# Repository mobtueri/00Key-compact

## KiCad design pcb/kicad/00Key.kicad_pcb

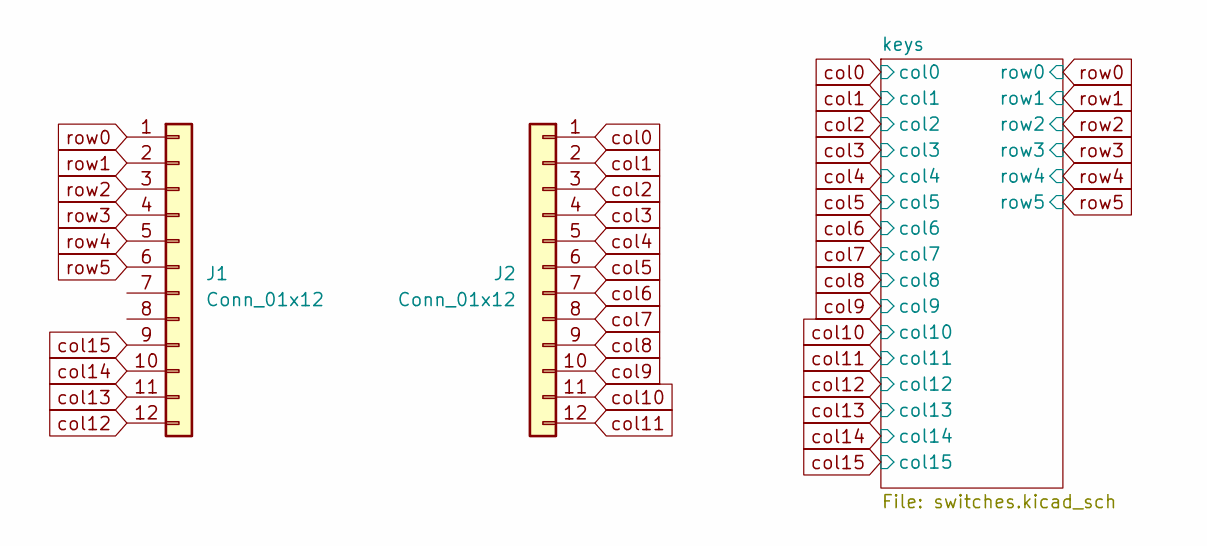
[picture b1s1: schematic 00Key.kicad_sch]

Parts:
J1, J2: Conn_01x12; PinSocket_1x12_P2.54mm_Horizontal

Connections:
col0: J2.1; also elsewhere on the board
col1: J2.2; also elsewhere on the board
col2: J2.3; also elsewhere on the board
col3: J2.4; also elsewhere on the board
col4: J2.5; also elsewhere on the board
col5: J2.6; also elsewhere on the board
col6: J2.7; also elsewhere on the board
col7: J2.8; also elsewhere on the board
col8: J2.9; also elsewhere on the board
col9: J2.10; also elsewhere on the board
col10: J2.11; also elsewhere on the board
col11: J2.12; also elsewhere on the board
col12: J1.12; also elsewhere on the board
col13: J1.11; also elsewhere on the board
col14: J1.10; also elsewhere on the board
col15: J1.9; also elsewhere on the board
row0: J1.1; also elsewhere on the board
row1: J1.2; also elsewhere on the board
row2: J1.3; also elsewhere on the board
row3: J1.4; also elsewhere on the board
row4: J1.5; also elsewhere on the board
row5: J1.6; also elsewhere on the board

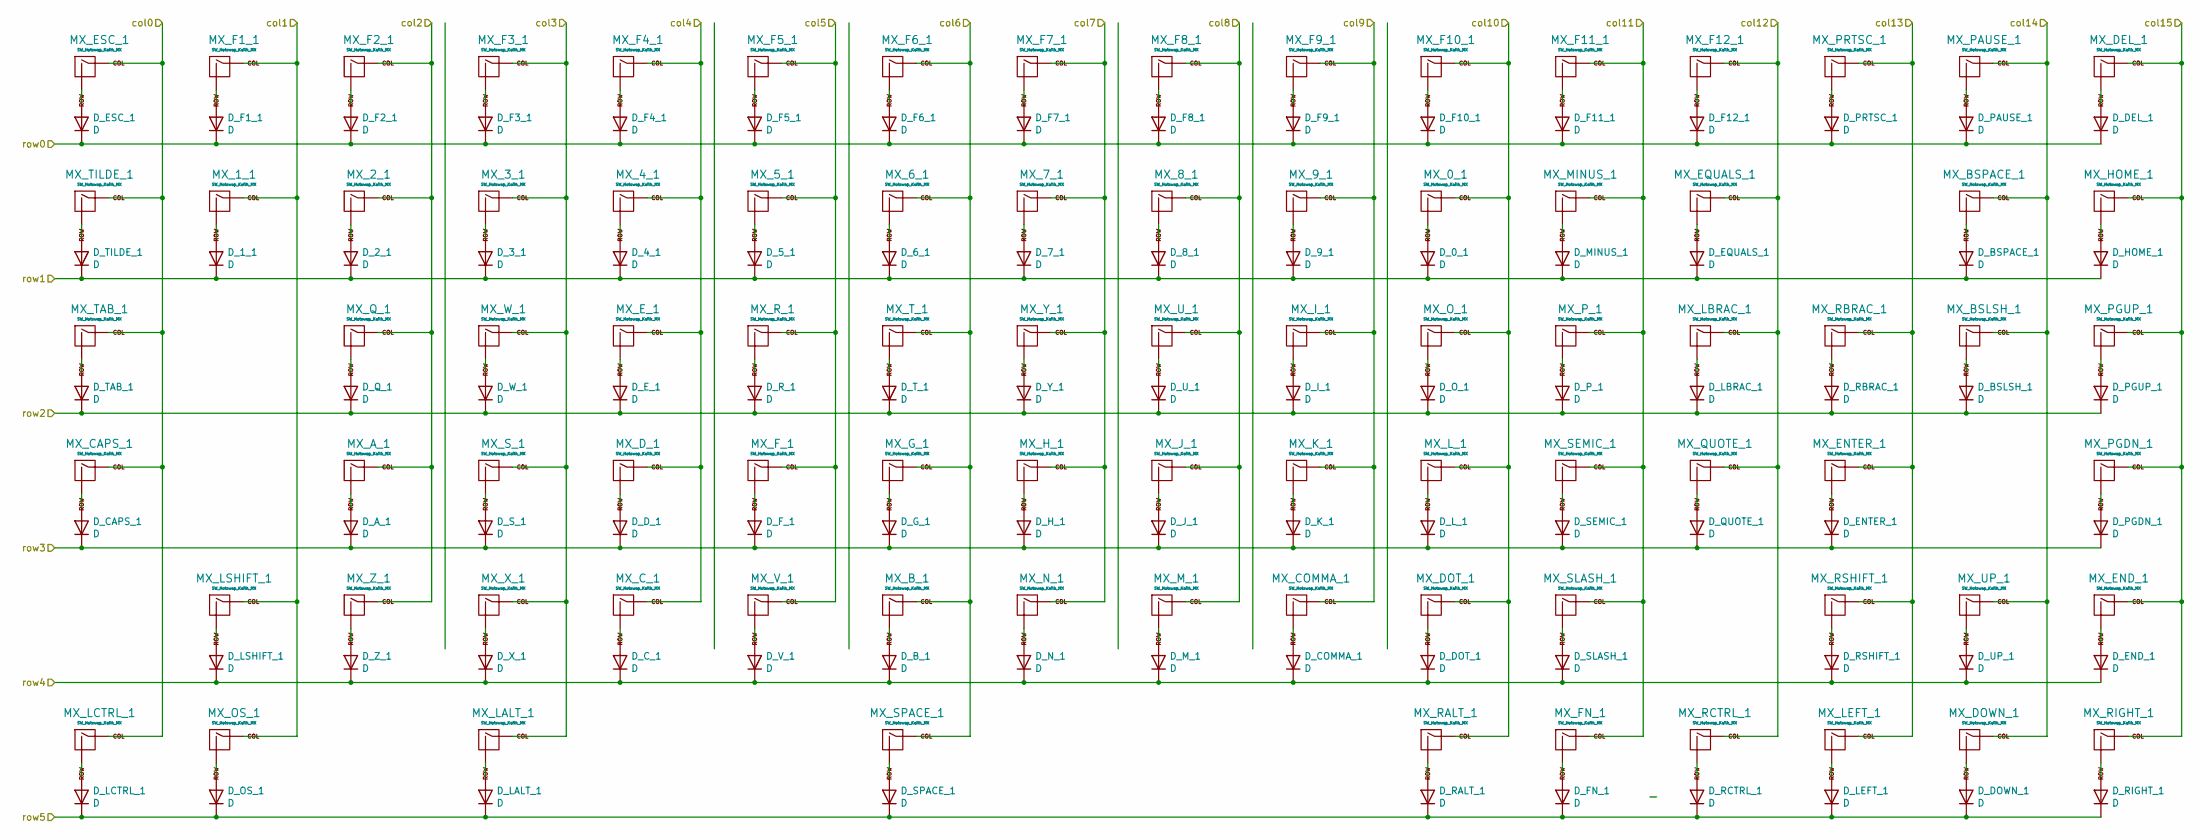
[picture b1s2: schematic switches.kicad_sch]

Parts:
D_0_1, D_1_1, D_2_1, D_3_1, D_4_1, D_5_1, D_6_1, D_7_1, D_8_1, D_9_1: D; D_SOD-123
D_A_1: D; D_SOD-123
D_BSLSH_1: D; D_SOD-123
D_BSPACE_1: D; D_SOD-123
D_B_1: D; D_SOD-123
D_CAPS_1: D; D_SOD-123
D_COMMA_1: D; D_SOD-123
D_C_1: D; D_SOD-123
D_DEL_1: D; D_SOD-123
D_DOT_1: D; D_SOD-123
D_DOWN_1: D; D_SOD-123
D_D_1: D; D_SOD-123
D_END_1: D; D_SOD-123
D_ENTER_1: D; D_SOD-123
D_EQUALS_1: D; D_SOD-123
D_ESC_1: D; D_SOD-123
D_E_1: D; D_SOD-123
D_F1_1, D_F2_1, D_F3_1, D_F4_1, D_F5_1, D_F6_1, D_F7_1, D_F8_1, D_F9_1, D_F10_1, D_F11_1, D_F12_1: D; D_SOD-123
D_FN_1: D; D_SOD-123
D_F_1: D; D_SOD-123
D_G_1: D; D_SOD-123
D_HOME_1: D; D_SOD-123
D_H_1: D; D_SOD-123
D_I_1: D; D_SOD-123
D_J_1: D; D_SOD-123
D_K_1: D; D_SOD-123
D_LALT_1: D; D_SOD-123
D_LBRAC_1: D; D_SOD-123
D_LCTRL_1: D; D_SOD-123
D_LEFT_1: D; D_SOD-123
D_LSHIFT_1: D; D_SOD-123
D_L_1: D; D_SOD-123
D_MINUS_1: D; D_SOD-123
D_M_1: D; D_SOD-123
D_N_1: D; D_SOD-123
D_OS_1: D; D_SOD-123
D_O_1: D; D_SOD-123
D_PAUSE_1: D; D_SOD-123
D_PGDN_1: D; D_SOD-123
D_PGUP_1: D; D_SOD-123
D_PRTSC_1: D; D_SOD-123
D_P_1: D; D_SOD-123
D_QUOTE_1: D; D_SOD-123
D_Q_1: D; D_SOD-123
D_RALT_1: D; D_SOD-123
D_RBRAC_1: D; D_SOD-123
D_RCTRL_1: D; D_SOD-123
D_RIGHT_1: D; D_SOD-123
D_RSHIFT_1: D; D_SOD-123
D_R_1: D; D_SOD-123
D_SEMIC_1: D; D_SOD-123
D_SLASH_1: D; D_SOD-123
D_SPACE_1: D; D_SOD-123
D_S_1: D; D_SOD-123
D_TAB_1: D; D_SOD-123
D_TILDE_1: D; D_SOD-123
D_T_1: D; D_SOD-123
D_UP_1: D; D_SOD-123
D_U_1: D; D_SOD-123
D_V_1: D; D_SOD-123
D_W_1: D; D_SOD-123
D_X_1: D; D_SOD-123
D_Y_1: D; D_SOD-123
D_Z_1: D; D_SOD-123
MX_0_1, MX_1_1, MX_2_1, MX_3_1, MX_4_1, MX_5_1, MX_6_1, MX_7_1, MX_8_1, MX_9_1: SW_Hotswap_Kailh_MX; SW_Hotswap_Kailh_MX_1.00u
MX_A_1: SW_Hotswap_Kailh_MX; SW_Hotswap_Kailh_MX_1.00u
MX_BSLSH_1: SW_Hotswap_Kailh_MX; SW_Hotswap_Kailh_MX_1.00u
MX_BSPACE_1: SW_Hotswap_Kailh_MX; SW_Hotswap_Kailh_MX_1.00u
MX_B_1: SW_Hotswap_Kailh_MX; SW_Hotswap_Kailh_MX_1.00u
MX_CAPS_1: SW_Hotswap_Kailh_MX; SW_Hotswap_Kailh_MX_1.00u
MX_COMMA_1: SW_Hotswap_Kailh_MX; SW_Hotswap_Kailh_MX_1.00u
MX_C_1: SW_Hotswap_Kailh_MX; SW_Hotswap_Kailh_MX_1.00u
MX_DEL_1: SW_Hotswap_Kailh_MX; SW_Hotswap_Kailh_MX_1.00u
MX_DOT_1: SW_Hotswap_Kailh_MX; SW_Hotswap_Kailh_MX_1.00u
MX_DOWN_1: SW_Hotswap_Kailh_MX; SW_Hotswap_Kailh_MX_1.00u
MX_D_1: SW_Hotswap_Kailh_MX; SW_Hotswap_Kailh_MX_1.00u
MX_END_1: SW_Hotswap_Kailh_MX; SW_Hotswap_Kailh_MX_1.00u
MX_ENTER_1: SW_Hotswap_Kailh_MX; SW_Hotswap_Kailh_MX_1.00u
MX_EQUALS_1: SW_Hotswap_Kailh_MX; SW_Hotswap_Kailh_MX_1.00u
MX_ESC_1: SW_Hotswap_Kailh_MX; SW_Hotswap_Kailh_MX_1.00u
MX_E_1: SW_Hotswap_Kailh_MX; SW_Hotswap_Kailh_MX_1.00u
MX_F1_1, MX_F2_1, MX_F3_1, MX_F4_1, MX_F5_1, MX_F6_1, MX_F7_1, MX_F8_1, MX_F9_1, MX_F10_1, MX_F11_1, MX_F12_1: SW_Hotswap_Kailh_MX; SW_Hotswap_Kailh_MX_1.00u
MX_FN_1: SW_Hotswap_Kailh_MX; SW_Hotswap_Kailh_MX_1.00u
MX_F_1: SW_Hotswap_Kailh_MX; SW_Hotswap_Kailh_MX_1.00u
MX_G_1: SW_Hotswap_Kailh_MX; SW_Hotswap_Kailh_MX_1.00u
MX_HOME_1: SW_Hotswap_Kailh_MX; SW_Hotswap_Kailh_MX_1.00u
MX_H_1: SW_Hotswap_Kailh_MX; SW_Hotswap_Kailh_MX_1.00u
MX_I_1: SW_Hotswap_Kailh_MX; SW_Hotswap_Kailh_MX_1.00u
MX_J_1: SW_Hotswap_Kailh_MX; SW_Hotswap_Kailh_MX_1.00u
MX_K_1: SW_Hotswap_Kailh_MX; SW_Hotswap_Kailh_MX_1.00u
MX_LALT_1: SW_Hotswap_Kailh_MX; SW_Hotswap_Kailh_MX_1.00u
MX_LBRAC_1: SW_Hotswap_Kailh_MX; SW_Hotswap_Kailh_MX_1.00u
MX_LCTRL_1: SW_Hotswap_Kailh_MX; SW_Hotswap_Kailh_MX_1.00u
MX_LEFT_1: SW_Hotswap_Kailh_MX; SW_Hotswap_Kailh_MX_1.00u
MX_LSHIFT_1: SW_Hotswap_Kailh_MX; SW_Hotswap_Kailh_MX_1.00u
MX_L_1: SW_Hotswap_Kailh_MX; SW_Hotswap_Kailh_MX_1.00u
MX_MINUS_1: SW_Hotswap_Kailh_MX; SW_Hotswap_Kailh_MX_1.00u
MX_M_1: SW_Hotswap_Kailh_MX; SW_Hotswap_Kailh_MX_1.00u
MX_N_1: SW_Hotswap_Kailh_MX; SW_Hotswap_Kailh_MX_1.00u
MX_OS_1: SW_Hotswap_Kailh_MX; SW_Hotswap_Kailh_MX_1.00u
MX_O_1: SW_Hotswap_Kailh_MX; SW_Hotswap_Kailh_MX_1.00u
MX_PAUSE_1: SW_Hotswap_Kailh_MX; SW_Hotswap_Kailh_MX_1.00u
MX_PGDN_1: SW_Hotswap_Kailh_MX; SW_Hotswap_Kailh_MX_1.00u
MX_PGUP_1: SW_Hotswap_Kailh_MX; SW_Hotswap_Kailh_MX_1.00u
MX_PRTSC_1: SW_Hotswap_Kailh_MX; SW_Hotswap_Kailh_MX_1.00u
MX_P_1: SW_Hotswap_Kailh_MX; SW_Hotswap_Kailh_MX_1.00u
MX_QUOTE_1: SW_Hotswap_Kailh_MX; SW_Hotswap_Kailh_MX_1.00u
MX_Q_1: SW_Hotswap_Kailh_MX; SW_Hotswap_Kailh_MX_1.00u
MX_RALT_1: SW_Hotswap_Kailh_MX; SW_Hotswap_Kailh_MX_1.00u
MX_RBRAC_1: SW_Hotswap_Kailh_MX; SW_Hotswap_Kailh_MX_1.00u
MX_RCTRL_1: SW_Hotswap_Kailh_MX; SW_Hotswap_Kailh_MX_1.00u
MX_RIGHT_1: SW_Hotswap_Kailh_MX; SW_Hotswap_Kailh_MX_1.00u
MX_RSHIFT_1: SW_Hotswap_Kailh_MX; SW_Hotswap_Kailh_MX_1.00u
MX_R_1: SW_Hotswap_Kailh_MX; SW_Hotswap_Kailh_MX_1.00u
MX_SEMIC_1: SW_Hotswap_Kailh_MX; SW_Hotswap_Kailh_MX_1.00u
MX_SLASH_1: SW_Hotswap_Kailh_MX; SW_Hotswap_Kailh_MX_1.00u
MX_SPACE_1: SW_Hotswap_Kailh_MX; SW_Hotswap_Kailh_MX_1.00u
MX_S_1: SW_Hotswap_Kailh_MX; SW_Hotswap_Kailh_MX_1.00u
MX_TAB_1: SW_Hotswap_Kailh_MX; SW_Hotswap_Kailh_MX_1.00u
MX_TILDE_1: SW_Hotswap_Kailh_MX; SW_Hotswap_Kailh_MX_1.00u
MX_T_1: SW_Hotswap_Kailh_MX; SW_Hotswap_Kailh_MX_1.00u
MX_UP_1: SW_Hotswap_Kailh_MX; SW_Hotswap_Kailh_MX_1.00u
MX_U_1: SW_Hotswap_Kailh_MX; SW_Hotswap_Kailh_MX_1.00u
MX_V_1: SW_Hotswap_Kailh_MX; SW_Hotswap_Kailh_MX_1.00u
MX_W_1: SW_Hotswap_Kailh_MX; SW_Hotswap_Kailh_MX_1.00u
MX_X_1: SW_Hotswap_Kailh_MX; SW_Hotswap_Kailh_MX_1.00u
MX_Y_1: SW_Hotswap_Kailh_MX; SW_Hotswap_Kailh_MX_1.00u
MX_Z_1: SW_Hotswap_Kailh_MX; SW_Hotswap_Kailh_MX_1.00u

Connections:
unnamed: D_0_1.2 (A), MX_0_1.2 (ROW)
unnamed: D_1_1.2 (A), MX_1_1.2 (ROW)
unnamed: D_2_1.2 (A), MX_2_1.2 (ROW)
unnamed: D_3_1.2 (A), MX_3_1.2 (ROW)
unnamed: D_4_1.2 (A), MX_4_1.2 (ROW)
unnamed: D_5_1.2 (A), MX_5_1.2 (ROW)
unnamed: D_6_1.2 (A), MX_6_1.2 (ROW)
unnamed: D_7_1.2 (A), MX_7_1.2 (ROW)
unnamed: D_8_1.2 (A), MX_8_1.2 (ROW)
unnamed: D_9_1.2 (A), MX_9_1.2 (ROW)
unnamed: D_A_1.2 (A), MX_A_1.2 (ROW)
unnamed: D_BSLSH_1.2 (A), MX_BSLSH_1.2 (ROW)
unnamed: D_BSPACE_1.2 (A), MX_BSPACE_1.2 (ROW)
unnamed: D_B_1.2 (A), MX_B_1.2 (ROW)
unnamed: D_CAPS_1.2 (A), MX_CAPS_1.2 (ROW)
unnamed: D_COMMA_1.2 (A), MX_COMMA_1.2 (ROW)
unnamed: D_C_1.2 (A), MX_C_1.2 (ROW)
unnamed: D_DEL_1.2 (A), MX_DEL_1.2 (ROW)
unnamed: D_DOT_1.2 (A), MX_DOT_1.2 (ROW)
unnamed: D_DOWN_1.2 (A), MX_DOWN_1.2 (ROW)
unnamed: D_D_1.2 (A), MX_D_1.2 (ROW)
unnamed: D_END_1.2 (A), MX_END_1.2 (ROW)
unnamed: D_ENTER_1.2 (A), MX_ENTER_1.2 (ROW)
unnamed: D_EQUALS_1.2 (A), MX_EQUALS_1.2 (ROW)
unnamed: D_ESC_1.2 (A), MX_ESC_1.2 (ROW)
unnamed: D_E_1.2 (A), MX_E_1.2 (ROW)
unnamed: D_F1_1.2 (A), MX_F1_1.2 (ROW)
unnamed: D_F2_1.2 (A), MX_F2_1.2 (ROW)
unnamed: D_F3_1.2 (A), MX_F3_1.2 (ROW)
unnamed: D_F4_1.2 (A), MX_F4_1.2 (ROW)
unnamed: D_F5_1.2 (A), MX_F5_1.2 (ROW)
unnamed: D_F6_1.2 (A), MX_F6_1.2 (ROW)
unnamed: D_F7_1.2 (A), MX_F7_1.2 (ROW)
unnamed: D_F8_1.2 (A), MX_F8_1.2 (ROW)
unnamed: D_F9_1.2 (A), MX_F9_1.2 (ROW)
unnamed: D_F10_1.2 (A), MX_F10_1.2 (ROW)
unnamed: D_F11_1.2 (A), MX_F11_1.2 (ROW)
unnamed: D_F12_1.2 (A), MX_F12_1.2 (ROW)
unnamed: D_FN_1.2 (A), MX_FN_1.2 (ROW)
unnamed: D_F_1.2 (A), MX_F_1.2 (ROW)
unnamed: D_G_1.2 (A), MX_G_1.2 (ROW)
unnamed: D_HOME_1.2 (A), MX_HOME_1.2 (ROW)
unnamed: D_H_1.2 (A), MX_H_1.2 (ROW)
unnamed: D_I_1.2 (A), MX_I_1.2 (ROW)
unnamed: D_J_1.2 (A), MX_J_1.2 (ROW)
unnamed: D_K_1.2 (A), MX_K_1.2 (ROW)
unnamed: D_LALT_1.2 (A), MX_LALT_1.2 (ROW)
unnamed: D_LBRAC_1.2 (A), MX_LBRAC_1.2 (ROW)
unnamed: D_LCTRL_1.2 (A), MX_LCTRL_1.2 (ROW)
unnamed: D_LEFT_1.2 (A), MX_LEFT_1.2 (ROW)
unnamed: D_LSHIFT_1.2 (A), MX_LSHIFT_1.2 (ROW)
unnamed: D_L_1.2 (A), MX_L_1.2 (ROW)
unnamed: D_MINUS_1.2 (A), MX_MINUS_1.2 (ROW)
unnamed: D_M_1.2 (A), MX_M_1.2 (ROW)
unnamed: D_N_1.2 (A), MX_N_1.2 (ROW)
unnamed: D_OS_1.2 (A), MX_OS_1.2 (ROW)
unnamed: D_O_1.2 (A), MX_O_1.2 (ROW)
unnamed: D_PAUSE_1.2 (A), MX_PAUSE_1.2 (ROW)
unnamed: D_PGDN_1.2 (A), MX_PGDN_1.2 (ROW)
unnamed: D_PGUP_1.2 (A), MX_PGUP_1.2 (ROW)
unnamed: D_PRTSC_1.2 (A), MX_PRTSC_1.2 (ROW)
unnamed: D_P_1.2 (A), MX_P_1.2 (ROW)
unnamed: D_QUOTE_1.2 (A), MX_QUOTE_1.2 (ROW)
unnamed: D_Q_1.2 (A), MX_Q_1.2 (ROW)
unnamed: D_RALT_1.2 (A), MX_RALT_1.2 (ROW)
unnamed: D_RBRAC_1.2 (A), MX_RBRAC_1.2 (ROW)
unnamed: D_RCTRL_1.2 (A), MX_RCTRL_1.2 (ROW)
unnamed: D_RIGHT_1.2 (A), MX_RIGHT_1.2 (ROW)
unnamed: D_RSHIFT_1.2 (A), MX_RSHIFT_1.2 (ROW)
unnamed: D_R_1.2 (A), MX_R_1.2 (ROW)
unnamed: D_SEMIC_1.2 (A), MX_SEMIC_1.2 (ROW)
unnamed: D_SLASH_1.2 (A), MX_SLASH_1.2 (ROW)
unnamed: D_SPACE_1.2 (A), MX_SPACE_1.2 (ROW)
unnamed: D_S_1.2 (A), MX_S_1.2 (ROW)
unnamed: D_TAB_1.2 (A), MX_TAB_1.2 (ROW)
unnamed: D_TILDE_1.2 (A), MX_TILDE_1.2 (ROW)
unnamed: D_T_1.2 (A), MX_T_1.2 (ROW)
unnamed: D_UP_1.2 (A), MX_UP_1.2 (ROW)
unnamed: D_U_1.2 (A), MX_U_1.2 (ROW)
unnamed: D_V_1.2 (A), MX_V_1.2 (ROW)
unnamed: D_W_1.2 (A), MX_W_1.2 (ROW)
unnamed: D_X_1.2 (A), MX_X_1.2 (ROW)
unnamed: D_Y_1.2 (A), MX_Y_1.2 (ROW)
unnamed: D_Z_1.2 (A), MX_Z_1.2 (ROW)
col0: MX_CAPS_1.1 (COL), MX_ESC_1.1 (COL), MX_LCTRL_1.1 (COL), MX_TAB_1.1 (COL), MX_TILDE_1.1 (COL); also elsewhere on the board
col1: MX_1_1.1 (COL), MX_F1_1.1 (COL), MX_LSHIFT_1.1 (COL), MX_OS_1.1 (COL); also elsewhere on the board
col2: MX_2_1.1 (COL), MX_A_1.1 (COL), MX_F2_1.1 (COL), MX_Q_1.1 (COL), MX_Z_1.1 (COL); also elsewhere on the board
col3: MX_3_1.1 (COL), MX_F3_1.1 (COL), MX_LALT_1.1 (COL), MX_S_1.1 (COL), MX_W_1.1 (COL), MX_X_1.1 (COL); also elsewhere on the board
col4: MX_4_1.1 (COL), MX_C_1.1 (COL), MX_D_1.1 (COL), MX_E_1.1 (COL), MX_F4_1.1 (COL); also elsewhere on the board
col5: MX_5_1.1 (COL), MX_F5_1.1 (COL), MX_F_1.1 (COL), MX_R_1.1 (COL), MX_V_1.1 (COL); also elsewhere on the board
col6: MX_6_1.1 (COL), MX_B_1.1 (COL), MX_F6_1.1 (COL), MX_G_1.1 (COL), MX_SPACE_1.1 (COL), MX_T_1.1 (COL); also elsewhere on the board
col7: MX_7_1.1 (COL), MX_F7_1.1 (COL), MX_H_1.1 (COL), MX_N_1.1 (COL), MX_Y_1.1 (COL); also elsewhere on the board
col8: MX_8_1.1 (COL), MX_F8_1.1 (COL), MX_J_1.1 (COL), MX_M_1.1 (COL), MX_U_1.1 (COL); also elsewhere on the board
col9: MX_9_1.1 (COL), MX_COMMA_1.1 (COL), MX_F9_1.1 (COL), MX_I_1.1 (COL), MX_K_1.1 (COL); also elsewhere on the board
col10: MX_0_1.1 (COL), MX_DOT_1.1 (COL), MX_F10_1.1 (COL), MX_L_1.1 (COL), MX_O_1.1 (COL), MX_RALT_1.1 (COL); also elsewhere on the board
col11: MX_F11_1.1 (COL), MX_FN_1.1 (COL), MX_MINUS_1.1 (COL), MX_P_1.1 (COL), MX_SEMIC_1.1 (COL), MX_SLASH_1.1 (COL); also elsewhere on the board
col12: MX_EQUALS_1.1 (COL), MX_F12_1.1 (COL), MX_LBRAC_1.1 (COL), MX_QUOTE_1.1 (COL), MX_RCTRL_1.1 (COL); also elsewhere on the board
col13: MX_ENTER_1.1 (COL), MX_LEFT_1.1 (COL), MX_PRTSC_1.1 (COL), MX_RBRAC_1.1 (COL), MX_RSHIFT_1.1 (COL); also elsewhere on the board
col14: MX_BSLSH_1.1 (COL), MX_BSPACE_1.1 (COL), MX_DOWN_1.1 (COL), MX_PAUSE_1.1 (COL), MX_UP_1.1 (COL); also elsewhere on the board
col15: MX_DEL_1.1 (COL), MX_END_1.1 (COL), MX_HOME_1.1 (COL), MX_PGDN_1.1 (COL), MX_PGUP_1.1 (COL), MX_RIGHT_1.1 (COL); also elsewhere on the board
row0: D_DEL_1.1 (K), D_ESC_1.1 (K), D_F1_1.1 (K), D_F2_1.1 (K), D_F3_1.1 (K), D_F4_1.1 (K), D_F5_1.1 (K), D_F6_1.1 (K), D_F7_1.1 (K), D_F8_1.1 (K), D_F9_1.1 (K), D_F10_1.1 (K), D_F11_1.1 (K), D_F12_1.1 (K), D_PAUSE_1.1 (K), D_PRTSC_1.1 (K); also elsewhere on the board
row1: D_0_1.1 (K), D_1_1.1 (K), D_2_1.1 (K), D_3_1.1 (K), D_4_1.1 (K), D_5_1.1 (K), D_6_1.1 (K), D_7_1.1 (K), D_8_1.1 (K), D_9_1.1 (K), D_BSPACE_1.1 (K), D_EQUALS_1.1 (K), D_HOME_1.1 (K), D_MINUS_1.1 (K), D_TILDE_1.1 (K); also elsewhere on the board
row2: D_BSLSH_1.1 (K), D_E_1.1 (K), D_I_1.1 (K), D_LBRAC_1.1 (K), D_O_1.1 (K), D_PGUP_1.1 (K), D_P_1.1 (K), D_Q_1.1 (K), D_RBRAC_1.1 (K), D_R_1.1 (K), D_TAB_1.1 (K), D_T_1.1 (K), D_U_1.1 (K), D_W_1.1 (K), D_Y_1.1 (K); also elsewhere on the board
row3: D_A_1.1 (K), D_CAPS_1.1 (K), D_D_1.1 (K), D_ENTER_1.1 (K), D_F_1.1 (K), D_G_1.1 (K), D_H_1.1 (K), D_J_1.1 (K), D_K_1.1 (K), D_L_1.1 (K), D_PGDN_1.1 (K), D_QUOTE_1.1 (K), D_SEMIC_1.1 (K), D_S_1.1 (K); also elsewhere on the board
row4: D_B_1.1 (K), D_COMMA_1.1 (K), D_C_1.1 (K), D_DOT_1.1 (K), D_END_1.1 (K), D_LSHIFT_1.1 (K), D_M_1.1 (K), D_N_1.1 (K), D_RSHIFT_1.1 (K), D_SLASH_1.1 (K), D_UP_1.1 (K), D_V_1.1 (K), D_X_1.1 (K), D_Z_1.1 (K); also elsewhere on the board
row5: D_DOWN_1.1 (K), D_FN_1.1 (K), D_LALT_1.1 (K), D_LCTRL_1.1 (K), D_LEFT_1.1 (K), D_OS_1.1 (K), D_RALT_1.1 (K), D_RCTRL_1.1 (K), D_RIGHT_1.1 (K), D_SPACE_1.1 (K); also elsewhere on the board

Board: 2 copper layers, 182 parts (86 on the bottom side), 106 nets, no tracks yet.

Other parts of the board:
H_KEYS_BL: MountingHole_2.2mm_M2_Pad
H_KEYS_BM: MountingHole_2.2mm_M2_Pad
H_KEYS_BR: MountingHole_2.2mm_M2_Pad
H_KEYS_TL: MountingHole_2.2mm_M2_Pad
H_KEYS_TM: MountingHole_2.2mm_M2_Pad
H_KEYS_TR: MountingHole_2.2mm_M2_Pad
H_PLATE_BL: MountingHole_2.2mm_M2_Pad
H_PLATE_BR: MountingHole_2.2mm_M2_Pad
H_PLATE_MB: MountingHole_2.2mm_M2_Pad
H_PLATE_TL: MountingHole_2.2mm_M2_Pad
H_PLATE_TM: MountingHole_2.2mm_M2_Pad
H_PLATE_TR: MountingHole_2.2mm_M2_Pad

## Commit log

2023-03-29 Modified schematic and pcb to use kailh hotswaps rather than MX+LED footprints
2023-03-29 fix gitignore
2023-04-01 Change diodes to smd, moved them to under switches, replaced teensy with header pins, reduced size of pcb
